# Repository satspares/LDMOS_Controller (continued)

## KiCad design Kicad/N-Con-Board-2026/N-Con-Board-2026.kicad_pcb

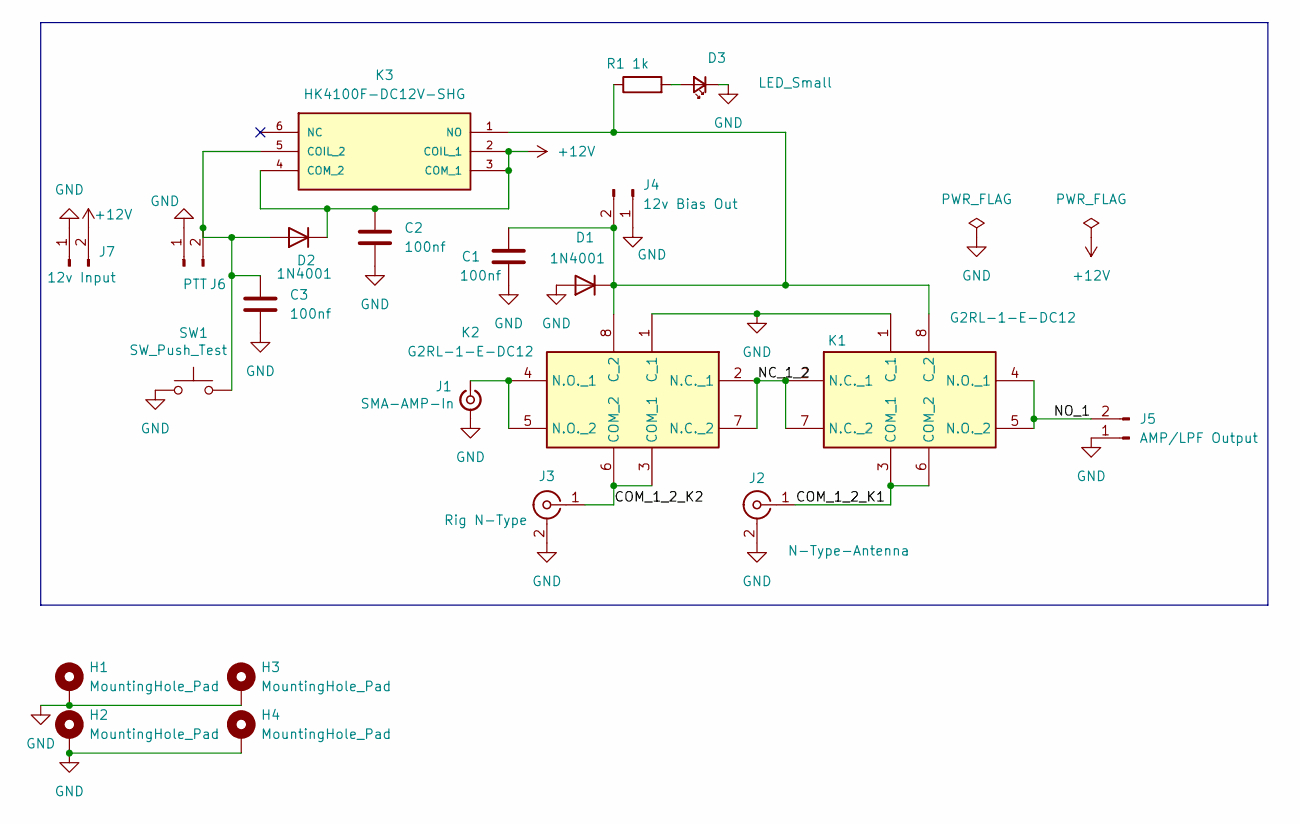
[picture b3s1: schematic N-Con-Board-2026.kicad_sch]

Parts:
C1, C2, C3: 100nf; C_Disc_D6.0mm_W2.5mm_P5.00mm
D1, D2: 1N4001; D_DO-41_SOD81_P10.16mm_Horizontal
D3: LED_Small; LED_D3.0mm
H1, H2, H3, H4: MountingHole_Pad; MountingHole_3.5mm_Pad_Via
J1: SMA-AMP-In; SMA_Amphenol_132134_Vertical
J2: N-Type-Antenna; N_TYPE
J3: Rig N-Type; N_TYPE
J4: 12v Bias Out; JST_EH_B2B-EH-A_1x02_P2.50mm_Vertical
J5: AMP/LPF Output; SolderWirePad_1x02_SMD_11x6mm
J6: PTT; JST_EH_B2B-EH-A_1x02_P2.50mm_Vertical
J7: 12v Input; JST_EH_B2B-EH-A_1x02_P2.50mm_Vertical
K1, K2: G2RL-1-E-DC12; G2RL1EDC24; Mouser Part Number 653-G2RL-1-E-DC12
K3: HK4100F-DC12V-SHG; HK4100FDC5VSHG; MANUFACTURER_PART_NUMBER HK4100F-DC5V-SHG
R1: 1k; R_Axial_DIN0207_L6.3mm_D2.5mm_P7.62mm_Horizontal
SW1: SW_Push_Test; SW_PUSH_6mm

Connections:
+12V: C2.1, D2.1 (K), J7.2, K3.2 (COIL_1), K3.3 (COM_1), K3.4 (COM_2)
/COM_1_2_K1: J2.1 (In), K1.3 (COM_1), K1.6 (COM_2)
/COM_1_2_K2: J3.1 (In), K2.3 (COM_1), K2.6 (COM_2)
/NC_1_2: K1.2 (N.C._1), K1.7 (N.C._2), K2.2 (N.C._1), K2.7 (N.C._2)
/NO_1: J5.2, K1.4 (N.O._1), K1.5 (N.O._2)
GND: C1.2, C2.2, C3.2, D1.2 (A), D3.1 (K), H1.1 (1_1), H2.1 (1_1), H3.1 (1_1), H4.1 (1_1), J1.2 (Ext), J2.2 (Ext), J3.2 (Ext), J4.1, J5.1, J6.1, J7.1, K1.1 (C_1), K2.1 (C_1), SW1.1
unnamed: C1.1, D1.1 (K), J4.2, K1.8 (C_2), K2.8 (C_2), K3.1 (NO), R1.1
unnamed: C3.1, D2.2 (A), J6.2, K3.5 (COIL_2), SW1.2
unnamed: D3.2 (A), R1.2
unnamed: J1.1 (In), K2.4 (N.O._1), K2.5 (N.O._2)

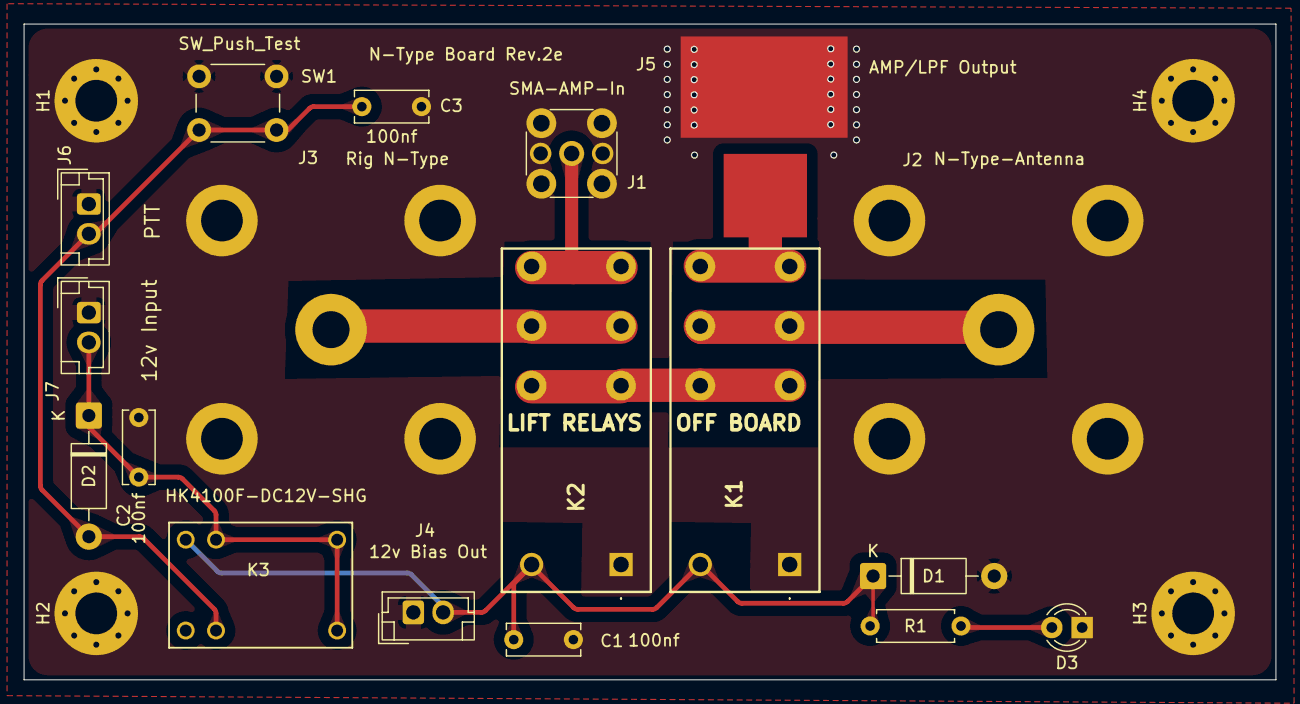
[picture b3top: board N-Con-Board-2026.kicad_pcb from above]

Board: 2 copper layers, 105.0 x 55.0 mm, 22 parts (0 on the bottom side), 10 nets.

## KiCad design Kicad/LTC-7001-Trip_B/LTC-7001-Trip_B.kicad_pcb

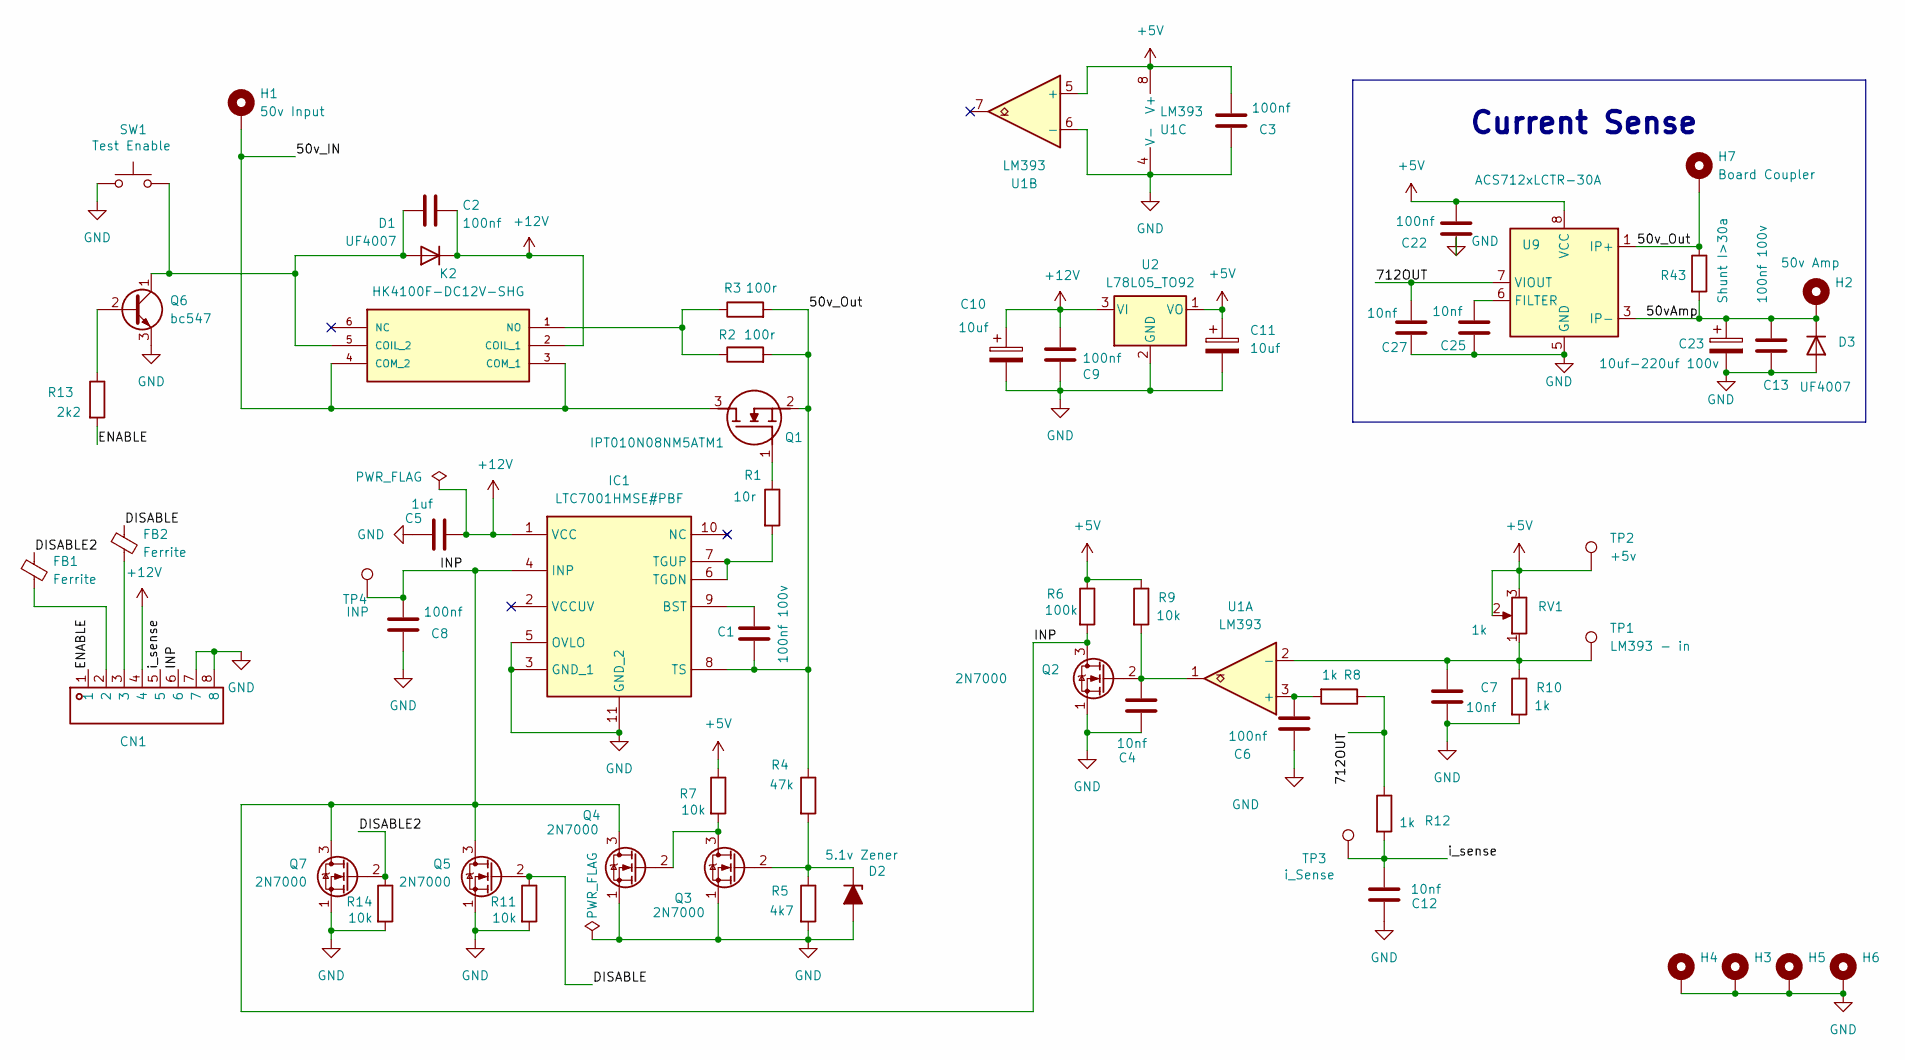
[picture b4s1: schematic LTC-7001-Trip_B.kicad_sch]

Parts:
C1, C13: 100nf 100v; C_Disc_D3.8mm_W2.6mm_P2.50mm
C2, C3, C6, C8, C9, C22: 100nf; C_Disc_D3.8mm_W2.6mm_P2.50mm
C4, C12: 10nf; C_Disc_D3.8mm_W2.6mm_P2.50mm
C5: 1uf; C_Disc_D3.8mm_W2.6mm_P2.50mm
C7, C25, C27: 10nf; C_Disc_D3.4mm_W2.1mm_P2.50mm
C10, C11: 10uf; C_Disc_D3.8mm_W2.6mm_P2.50mm
C23: 10uf-220uf 100v; CP_Radial_D10.0mm_P5.00mm
CN1: CONN-TH_8P-P2.54_KF141R-2.54-8P; Manufacturer Part KF141R-2.54-8P; LCSC Part Name 1x6P 2.54mm 每排P数:8 排数:1
D1, D3: UF4007; D_DO-41_SOD81_P10.16mm_Horizontal
D2: 5.1v Zener; D_DO-35_SOD27_P7.62mm_Horizontal
FB1, FB2: Ferrite; R_1206_3216Metric_Pad1.30x1.75mm_HandSolder
H1: 50v Input; Power-Pad
H2: 50v Amp; Power-Pad
H3, H4, H5, H6: MountingHole_Pad; MountingHole_3.5mm_Pad_Via
H7: Board Coupler; MountingHole_3.5mm_Pad_Via
IC1: LTC7001HMSE#PBF; SOP50P490X110-11N; Manufacturer_Part_Number LTC7001HMSE#PBF; Mouser Part Number 584-LTC7001HMSEPBF
K2: HK4100F-DC12V-SHG; HK4100FDC5VSHG; MANUFACTURER_PART_NUMBER HK4100F-DC5V-SHG
Q1: IPT010N08NM5ATM1; IAUT150N10S5N035ATMA1; Manufacturer_Part_Number FDP083N15A-F102; Mouser Part Number 512-FDP083N15A_F102
Q2, Q3, Q4, Q5, Q7: 2N7000; TO-92-mod2
Q6: bc547; TO-92_HandSolder
R1: 10r; R_Axial_DIN0207_L6.3mm_D2.5mm_P7.62mm_Horizontal
R2, R3: 100r; RESC11050X120N
R4: 47k; R_Axial_DIN0207_L6.3mm_D2.5mm_P7.62mm_Horizontal
R5: 4k7; R_Axial_DIN0207_L6.3mm_D2.5mm_P7.62mm_Horizontal
R6: 100k; R_Axial_DIN0207_L6.3mm_D2.5mm_P7.62mm_Horizontal
R7, R9, R11, R14: 10k; R_Axial_DIN0207_L6.3mm_D2.5mm_P7.62mm_Horizontal
R8, R10, R12: 1k; R_Axial_DIN0207_L6.3mm_D2.5mm_P7.62mm_Horizontal
R13: 2k2; R_Axial_DIN0207_L6.3mm_D2.5mm_P7.62mm_Horizontal
R43: Shunt I>30a; RESC11050X120N
RV1: 1k
SW1: Test Enable; SW_PUSH_6mm
TP1: LM393 - in; TestPoint_THTPad_3.0x3.0mm_Drill1.5mm
TP2: +5v; TestPoint_THTPad_3.0x3.0mm_Drill1.5mm
TP3: i_Sense; TestPoint_THTPad_3.0x3.0mm_Drill1.5mm
TP4: INP; TestPoint_THTPad_3.0x3.0mm_Drill1.5mm
U1: LM393; DIP-8_W7.62mm_Socket
U2: L78L05_TO92; TO-92_Inline-mod
U9: ACS712xLCTR-30A; SOIC-8_3.9x4.9mm_P1.27mm

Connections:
+5V: C3.2, C11.1, C22.1, R6.1, R7.1, R9.1, RV1.2, RV1.3, TP2.1 (1_1), U1.5 (+), U1.8 (V+), U2.1 (VO), U9.8 (VCC)
+12V: C2.2, C5.2, C9.2, C10.1, CN1.4, D1.1 (K), IC1.1 (VCC), K2.2 (COIL_1), U2.3 (VI)
/50vAmp: C13.1, C23.1, D3.1 (K), H2.1 (1_1), R43.2, U9.3 (IP-), U9.4 (IP-)
/50v_IN: H1.1 (1_1), K2.3 (COM_1), K2.4 (COM_2), Q1.3 (S)
/50v_Out: C1.2, H7.1 (1_1), IC1.8 (TS), Q1.2 (D), R2.2, R3.2, R4.1, R43.1, U9.1 (IP+), U9.2 (IP+)
/712OUT: C27.1, R8.1, R12.1, U9.7 (VIOUT)
/DISABLE: FB2.1, Q5.2 (G), R11.1
/DISABLE2: FB1.1, Q7.2 (G), R14.1
/ENABLE: CN1.1, R13.2
/INP: C8.2, CN1.6, IC1.4 (INP), Q2.3 (D), Q4.3 (D), Q5.3 (D), Q7.3 (D), R6.2, TP4.1 (1_1)
/i_sense: C12.1, CN1.5, R12.2, TP3.1 (1_1)
GND: C3.1, C4.1, C5.1, C6.1, C7.1, C8.1, C9.1, C10.2, C11.2, C12.2, C13.2, C22.2, C23.2, C25.1, C27.2, CN1.7, CN1.8, D2.2 (A), D3.2 (A), H3.1 (1_1), H4.1 (1_1), H5.1 (1_1), H6.1 (1_1), IC1.3 (GND_1), IC1.5 (OVLO), IC1.11 (GND_2), Q2.1 (S), Q3.1 (S), Q4.1 (S), Q5.1 (S), Q6.3 (E), Q7.1 (S), R5.2, R10.2, R11.2, R14.2, SW1.1, U1.4 (V-), U1.6 (-), U2.2 (GND), U9.5 (GND)
unnamed: CN1.2, FB1.2
unnamed: CN1.3, FB2.2
unnamed: C2.1, D1.2 (A), K2.5 (COIL_2), Q6.1 (C), SW1.2
unnamed: D2.1 (K), Q3.2 (G), R4.2, R5.1
unnamed: C1.1, IC1.9 (BST)
unnamed: IC1.6 (TGDN), IC1.7 (TGUP), R1.2
unnamed: K2.1 (NO), R2.1, R3.1
unnamed: Q1.1 (G), R1.1
unnamed: C4.2, Q2.2 (G), R9.2, U1.1
unnamed: Q3.3 (D), Q4.2 (G), R7.2
unnamed: Q6.2 (B), R13.1
unnamed: C6.2, R8.2, U1.3 (+)
unnamed: C7.2, R10.1, RV1.1, TP1.1 (1_1), U1.2 (-)
unnamed: C25.2, U9.6 (FILTER)

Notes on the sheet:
Current Sense

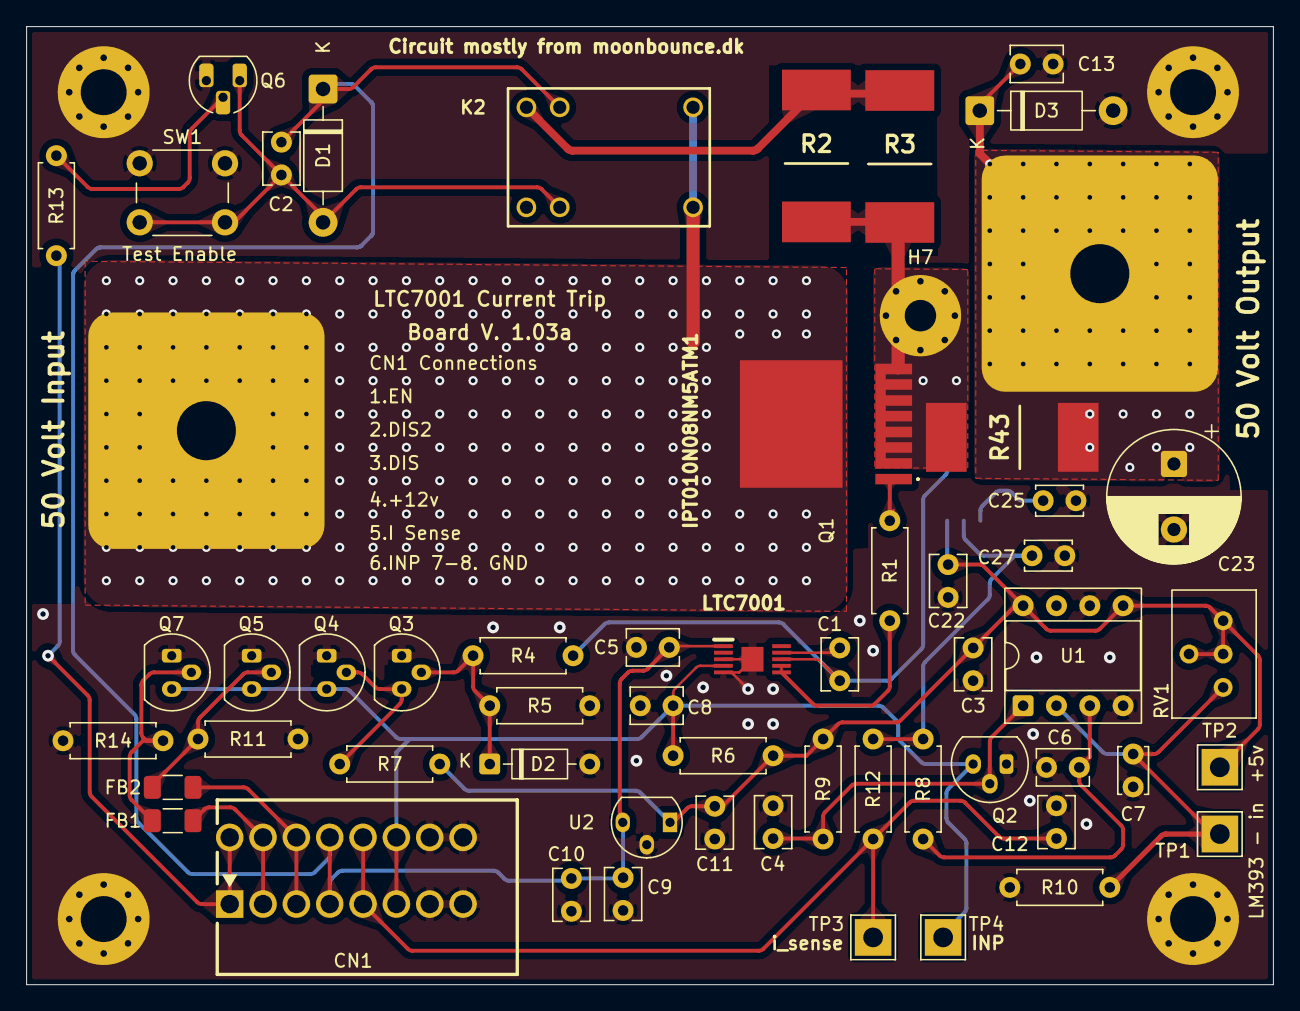
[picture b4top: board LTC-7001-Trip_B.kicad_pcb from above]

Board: 2 copper layers, 95.0 x 73.0 mm, 63 parts (1 on the bottom side), 26 nets.

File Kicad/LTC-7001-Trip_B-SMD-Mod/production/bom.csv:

Designator,Footprint,Quantity,Value,LCSC Part #
"C1, C13",C_Disc_D3.8mm_W2.6mm_P2.50mm,2,100nf 100v,
"C10, C11",C_Disc_D3.8mm_W2.6mm_P2.50mm,2,10uf,
"C12, C4",C_Disc_D3.8mm_W2.6mm_P2.50mm,2,10nf,
"C2, C22, C3, C6, C8, C9",C_Disc_D3.8mm_W2.6mm_P2.50mm,6,100nf,
C23,CP_Radial_D10.0mm_P5.00mm,1,10uf-220uf 100v,
"C25, C27, C7",C_Disc_D3.4mm_W2.1mm_P2.50mm,3,10nf,
C5,C_Disc_D3.8mm_W2.6mm_P2.50mm,1,1uf,
CN1,CONN-TH_8P-P2.54_KF141R-2.54-8P,1,~,
"D1, D3",D_DO-41_SOD81_P10.16mm_Horizontal,2,UF4007,
D2,D_DO-35_SOD27_P7.62mm_Horizontal,1,5.1v Zener,
"FB1, FB2",1206,2,Ferrite,
IC1,SOP50P490X110-11N,1,LTC7001HMSE#PBF,
K2,HK4100FDC5VSHG,1,HK4100F-DC12V-SHG,
Q1,IAUT150N10S5N035ATMA1,1,IPT010N08NM5ATM1,
"Q2, Q3, Q4, Q5, Q7",TO-92-mod2,5,2N7000,
Q6,TO-92_HandSolder,1,bc547,
R1,R_Axial_DIN0207_L6.3mm_D2.5mm_P7.62mm_Horizontal,1,10r,
"R10, R12, R8",R_Axial_DIN0207_L6.3mm_D2.5mm_P7.62mm_Horizontal,3,1k,
"R11, R14, R7, R9",R_Axial_DIN0207_L6.3mm_D2.5mm_P7.62mm_Horizontal,4,10k,
R13,R_Axial_DIN0207_L6.3mm_D2.5mm_P7.62mm_Horizontal,1,2k2,
"R2, R3",RESC11050X120N,2,100r,
R4,R_Axial_DIN0207_L6.3mm_D2.5mm_P7.62mm_Horizontal,1,47k,
R43,RESC11050X120N,1,Shunt I>30a,
R5,R_Axial_DIN0207_L6.3mm_D2.5mm_P7.62mm_Horizontal,1,4k7,
R6,R_Axial_DIN0207_L6.3mm_D2.5mm_P7.62mm_Horizontal,1,100k,
RV1,Potentiometer_Bourns_3296W_Vertical,1,1k,
SW1,SW_PUSH_6mm,1,Test Enable,
TP1,TestPoint_THTPad_3.0x3.0mm_Drill1.5mm,1,LM393 - in,
TP2,TestPoint_THTPad_3.0x3.0mm_Drill1.5mm,1,+5v,
TP3,TestPoint_THTPad_3.0x3.0mm_Drill1.5mm,1,i_Sense,
TP4,TestPoint_THTPad_3.0x3.0mm_Drill1.5mm,1,INP,
U1,SOP-8_3.76x4.96mm_P1.27mm,1,LMV393,
U2,TO-92_Inline-mod,1,L78L05_TO92,
U9,SOIC-8_3.9x4.9mm_P1.27mm,1,ACS712xLCTR-30A,

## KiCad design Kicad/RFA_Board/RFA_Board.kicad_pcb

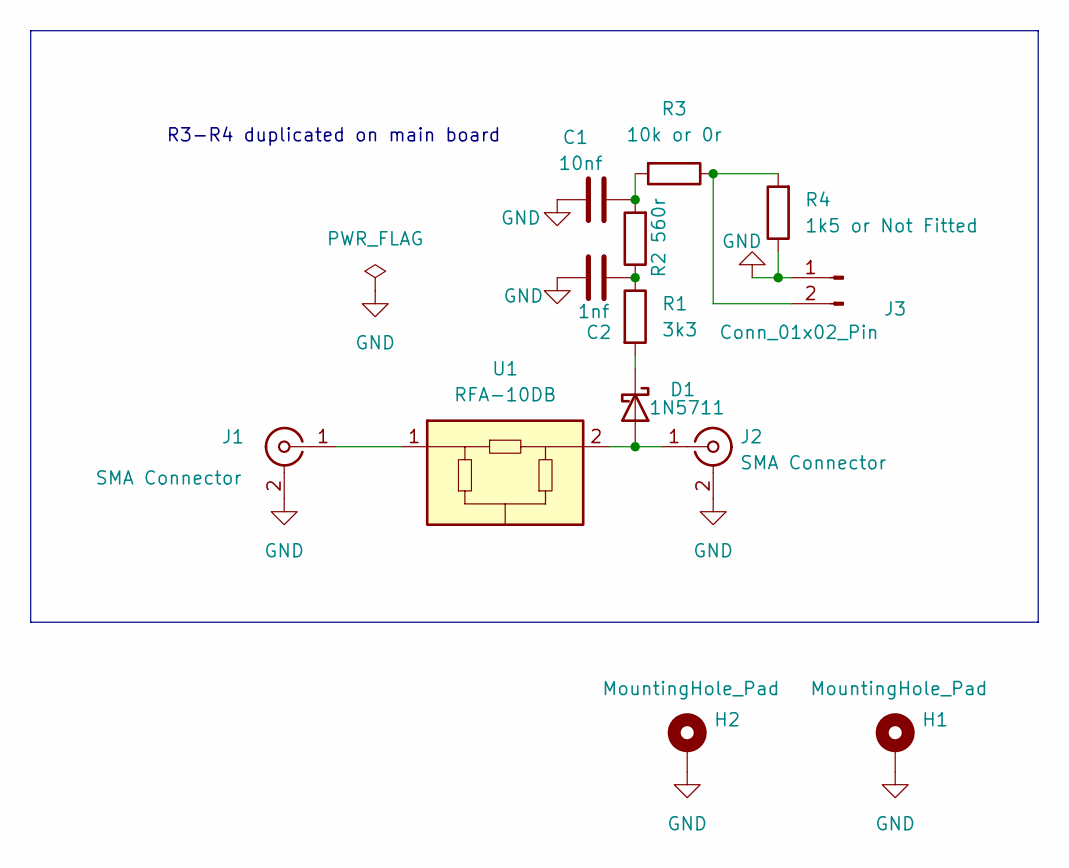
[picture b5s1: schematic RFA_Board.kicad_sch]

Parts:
C1: 10nf; C_1206_3216Metric_Pad1.33x1.80mm_HandSolder-mod
C2: 1nf; C_1206_3216Metric_Pad1.33x1.80mm_HandSolder-mod
D1: 1N5711; D_MELF-RM10_Universal_Handsoldering-mod
H1, H2: MountingHole_Pad; MountingHole_3.5mm_Pad_Via
J1, J2: SMA Connector; SMA_Molex_73251-2200_Horizontal_MOD
J3: Conn_01x02_Pin; SolderWirePad_1x02_SMD_12.5x8mm
R1: 3k3; R_1206_3216Metric_Pad1.30x1.75mm_HandSolder-mod
R2: 560r; R_1206_3216Metric_Pad1.30x1.75mm_HandSolder-mod
R3: 10k or 0r; R_1206_3216Metric_Pad1.30x1.75mm_HandSolder-mod
R4: 1k5 or Not Fitted; R_1206_3216Metric_Pad1.30x1.75mm_HandSolder-mod
U1: RFA-10DB; RFA Attenuator

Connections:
GND: C1.1, C2.1, H1.1 (1_1), H2.1 (1_1), J1.2 (Ext), J2.2 (Ext), J3.1, R4.1
unnamed: C1.2, R2.2, R3.2
unnamed: C2.2, R1.1, R2.1
unnamed: D1.2 (A), J2.1 (In), U1.2
unnamed: D1.1 (K), R1.2
unnamed: J1.1 (In), U1.1
unnamed: J3.2, R3.1, R4.2

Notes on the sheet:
R3-R4 duplicated on main board

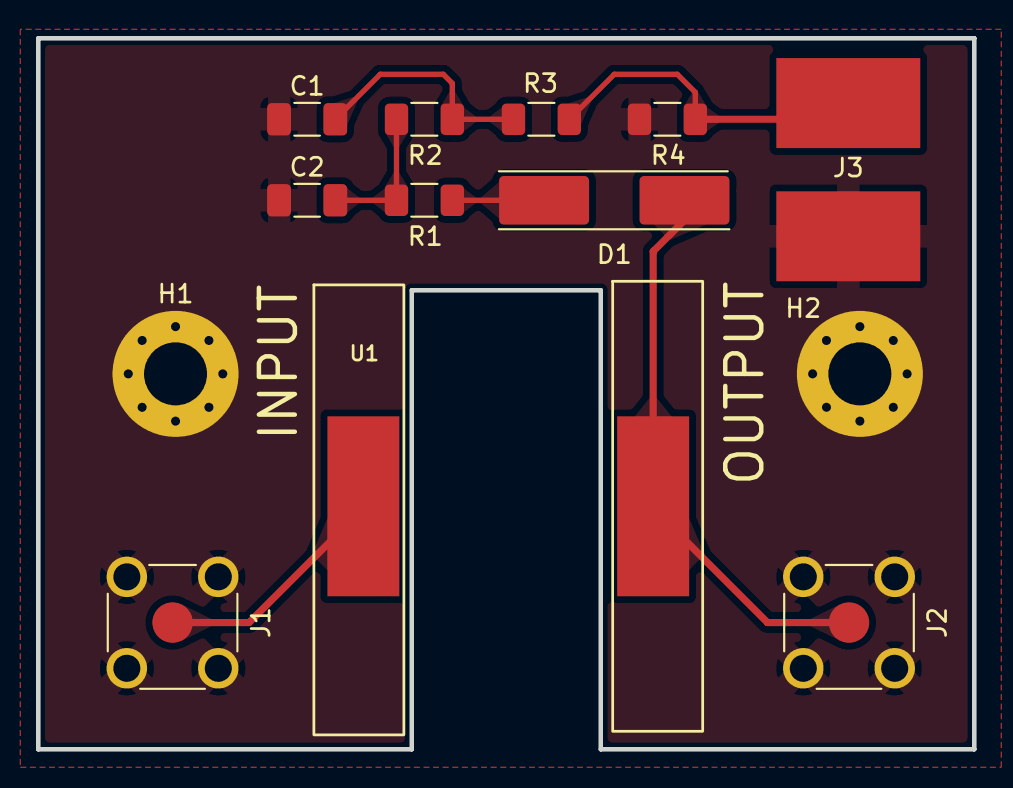
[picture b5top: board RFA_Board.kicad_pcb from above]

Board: 2 copper layers, 52.0 x 39.5 mm, 13 parts (0 on the bottom side), 7 nets.

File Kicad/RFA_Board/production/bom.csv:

Designator,Footprint,Quantity,Value,LCSC Part #
C1,1206,1,10nf,
C2,1206,1,1nf,
D1,D_MELF-RM10_Universal_Handsoldering,1,1N5711,
"J1, J2",SMA_Molex_73251-2200_Horizontal_MOD,2,SMA Connector,
J3,SolderWirePad_1x02_SMD_5x8mm,1,Conn_01x02_Pin,
R1,1206,1,3k3,
R2,1206,1,560r,
R3,1206,1,10k or 0r,
R4,1206,1,1k5 or Not Fitted,
U1,RFA Attenuator,1,RFA-10DB,

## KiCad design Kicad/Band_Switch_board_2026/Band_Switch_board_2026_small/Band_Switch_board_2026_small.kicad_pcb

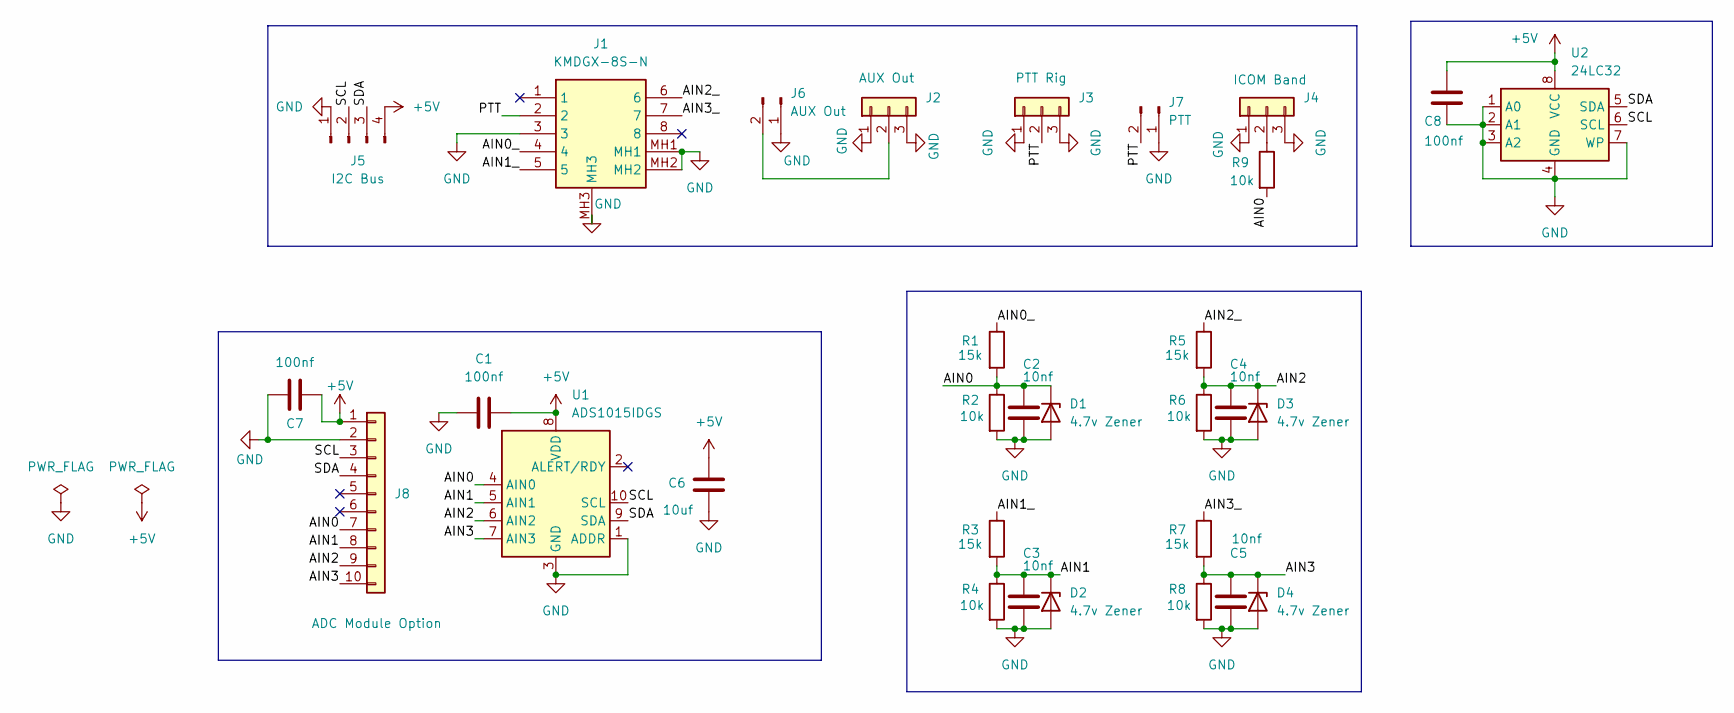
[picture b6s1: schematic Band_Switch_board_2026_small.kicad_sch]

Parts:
C1, C7, C8: 100nf; C_Disc_D6.0mm_W2.5mm_P5.00mm
C2, C3, C4, C5: 10nf; C_Disc_D3.4mm_W2.1mm_P2.50mm
C6: 10uf; CP_Radial_Tantal_D5.0mm_P2.50mm
D1, D2, D3, D4: 4.7v Zener; D_DO-35_SOD27_P7.62mm_Horizontal
J1: KMDGX-8S-N; KMDGX8SN; Mouser Part Number 806-KMDGX-8S-N
J2: AUX Out; BarrelJack__Horizontal_Band_Switch
J3: PTT Rig; BarrelJack__Horizontal_Band_Switch
J4: ICOM Band; BarrelJack__Horizontal_Band_Switch
J5: I2C Bus; JST_EH_B4B-EH-A_1x04_P2.50mm_Vertical
J6: AUX Out; JST_EH_B2B-EH-A_1x02_P2.50mm_Vertical
J7: PTT; JST_EH_B2B-EH-A_1x02_P2.50mm_Vertical
J8: ADC Module Option; PinHeader_1x10_P2.54mm_Vertical_ADC
R1, R3, R5, R7: 15k; R_Axial_DIN0207_L6.3mm_D2.5mm_P7.62mm_Horizontal
R2, R4, R6, R8, R9: 10k; R_Axial_DIN0207_L6.3mm_D2.5mm_P7.62mm_Horizontal
U1: ADS1015IDGS; TSSOP-10_3x3mm_P0.5mm
U2: 24LC32; DIP-8_W7.62mm_Socket

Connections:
+5V: C1.2, C6.1, C7.2, C8.2, J5.4, J8.1, U1.8 (VDD), U2.8 (VCC)
/AIN0: C2.1, D1.1 (K), J8.7, R1.2, R2.1, R9.2, U1.4 (AIN0)
/AIN0_: J1.4, R1.1
/AIN1: C3.1, D2.1 (K), J8.8, R3.2, R4.1, U1.5 (AIN1)
/AIN1_: J1.5, R3.1
/AIN2: C4.1, D3.1 (K), J8.9, R5.2, R6.1, U1.6 (AIN2)
/AIN2_: J1.6, R5.1
/AIN3: C5.1, D4.1 (K), J8.10, R7.2, R8.1, U1.7 (AIN3)
/AIN3_: J1.7, R7.1
/PTT: J1.2, J3.2, J7.2
/SCL: J5.2, J8.3, U1.10 (SCL), U2.6 (SCL)
/SDA: J5.3, J8.4, U1.9 (SDA), U2.5 (SDA)
GND: C1.1, C2.2, C3.2, C4.2, C5.2, C6.2, C7.1, C8.1, D1.2 (A), D2.2 (A), D3.2 (A), D4.2 (A), J1.3, J1.MH1, J1.MH2, J1.MH3, J2.1, J2.3, J3.1, J3.3, J4.1, J4.3, J5.1, J6.1, J7.1, J8.2, R2.2, R4.2, R6.2, R8.2, U1.1 (ADDR), U1.3 (GND), U2.1 (A0), U2.2 (A1), U2.3 (A2), U2.4 (GND), U2.7 (WP)
unnamed: J2.2, J6.2
unnamed: J4.2, R9.1

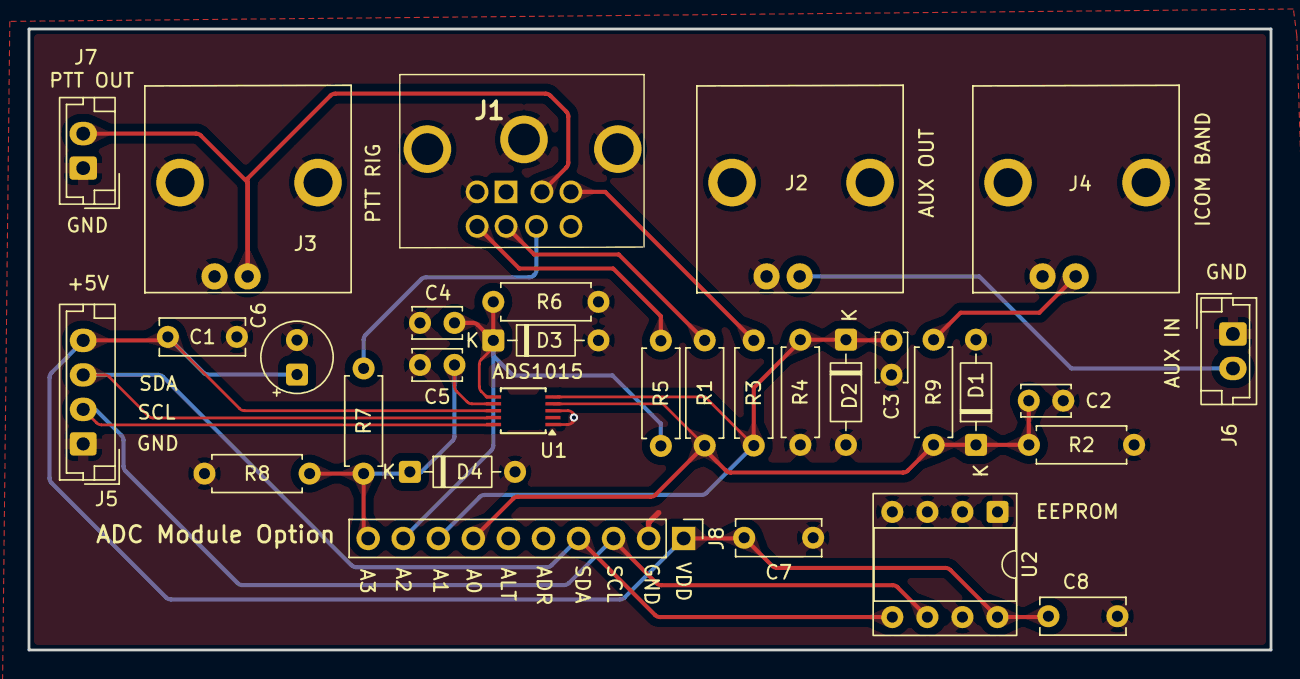
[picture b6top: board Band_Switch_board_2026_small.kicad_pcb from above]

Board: 2 copper layers, 90.0 x 45.0 mm, 31 parts (0 on the bottom side), 15 nets.

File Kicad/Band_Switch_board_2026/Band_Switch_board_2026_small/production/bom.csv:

Designator,Footprint,Quantity,Value,LCSC Part #
"C1, C7, C8",C_Disc_D6.0mm_W2.5mm_P5.00mm,3,100nf,
"C2, C3, C4, C5",C_Disc_D3.4mm_W2.1mm_P2.50mm,4,10nf,
C6,CP_Radial_Tantal_D5.0mm_P2.50mm,1,10uf,
"D1, D2, D3, D4",D_DO-35_SOD27_P7.62mm_Horizontal,4,4.7v Zener,
J1,KMDGX8SN,1,KMDGX-8S-N,
J2,BarrelJack__Horizontal_Band_Switch,1,AUX Out,
J3,BarrelJack__Horizontal_Band_Switch,1,PTT Rig,
J4,BarrelJack__Horizontal_Band_Switch,1,ICOM Band,
J5,JST_EH_B4B-EH-A_1x04_P2.50mm_Vertical,1,I2C Bus,
J6,JST_EH_B2B-EH-A_1x02_P2.50mm_Vertical,1,AUX Out,
J7,JST_EH_B2B-EH-A_1x02_P2.50mm_Vertical,1,PTT,
J8,PinHeader_1x10_P2.54mm_Vertical_ADC,1,ADC Module Option,
"R1, R3, R5, R7",R_Axial_DIN0207_L6.3mm_D2.5mm_P7.62mm_Horizontal,4,15k,
"R2, R4, R6, R8, R9",R_Axial_DIN0207_L6.3mm_D2.5mm_P7.62mm_Horizontal,5,10k,
U1,TSSOP-10_3x3mm_P0.5mm,1,ADS1015IDGS,
U2,DIP-8_W7.62mm_Socket,1,24LC32,

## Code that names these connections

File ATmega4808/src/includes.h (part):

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createSafeString(MainText2,30," --- YOUR CALL --- ")

/* ======= SWR Progress Bar Max Display eg. 200=2.00 swr 300=3.00 swr or other swr value * 100 ======== */
const uint16_t swrRangeMax = 250;  // 250 swr graph max is swr 2.50
const uint16_t powerRangeMax = 800; // Max Power graph range eg. 600=600 watts

/* ======= TX delay before tx needed for slow relays ======== */
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#endif


const uint16_t SWRColorChange = 16;         //change swr bar color on high swr (swr * 10 eg 16 = 1.6swr )
const uint16_t SWROriginalColor = 0xFC00;   // orange
const uint16_t SWRHighSWRColor = 0xF800;    //red

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// ************** Page 1 power calc page ***********
// Display controls
const uint16_t startPage_band_text = 0x5030;        //String 21 dec
const uint16_t startPage_swr_text = 0x5060;         //String 21 dec also used on page 4 swr calc
const uint16_t power_display_startPage = 0x2402;    // power in watt display
const uint16_t display_power_set_point = 0x2404; // power set point

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const uint8_t band4Mtr_switch =     0b00000001;

// MCP23017 port B pins
const uint8_t A600BIAS = 8;         //< pin GPB0 (1) of the MCP23017. via. resistor split
const uint8_t AUX_FAN_POWER = 9;    //< pin GPB1 (2) of the MCP23017. Transistor Base
const uint8_t FAN_POWER = 10;       //< pin GPB2 (3) of the MCP23017.
const uint8_t EN_I_BOARD = 11;      //< pin GPB3 (4) of the MCP23017.
const uint8_t BIAS12V = 12;         //< pin GPB4 (5) of the MCP23017.
const uint8_t SWR_TRIP = 13;        //< pin GPB5 (6) of the MCP23017.
const uint8_t ANTSWITCH = 14;       //< pin GPB6 (7) of the MCP23017.
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#define REF2        A6
#define ID_IN       A5
#define RFSENSE     A4
#define PTT         12 // new
#define LED_I       9  // DX-World errors
#define LED_PO      10 
#define LED_SWR     15 
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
